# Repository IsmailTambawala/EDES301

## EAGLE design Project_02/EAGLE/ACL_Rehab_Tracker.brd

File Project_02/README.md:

# ACL Rehab Tracker PCB (Project 2)

Compact PCB spin of the Project 1 ACL Rehab Tracker, prepared for fabrication and assembly. This folder holds all design sources and manufacturing outputs.

## Contents
- `ACL Rehab Tracker Schematics.pdf` – quick schematic reference.
- `Docs/` – PDF plots of top/bottom layers and routing.
- `EAGLE/` – editable EAGLE design files (`.sch`, `.brd`, and custom library).
- `ACL_Rehab_Tracker_BOM.csv` – bill of materials for sourcing parts.
- `MFG/CAMOutputs/` – production package:
  - `GerberFiles/` – copper, mask, paste, and silkscreen layers.
  - `DrillFiles/` – NC drill file.
  - `Assembly/` – pick-and-place (front/back) and assembly notes.

## How to build
1) Review the schematic PDF for component intent and placements.  
2) If editing, open `EAGLE/ACL_Rehab_Tracker.sch` and `.brd`, then regenerate CAM if changes are made.  
3) Zip `MFG/CAMOutputs/GerberFiles` and `DrillFiles` for PCB fab.  
4) Send `MFG/CAMOutputs/Assembly` files with the BOM to your assembler for PnP.  
5) Use the Project 1 firmware/software with this board; no firmware changes are required for a fab-only spin.

## Notes
- Designed as a compact, production-ready version of the original prototype.  
- Check part availability against `ACL_Rehab_Tracker_BOM.csv` before ordering to avoid substitutions.  
- If your fab expects a single archive, include the gerbers, drill, and both PnP files.

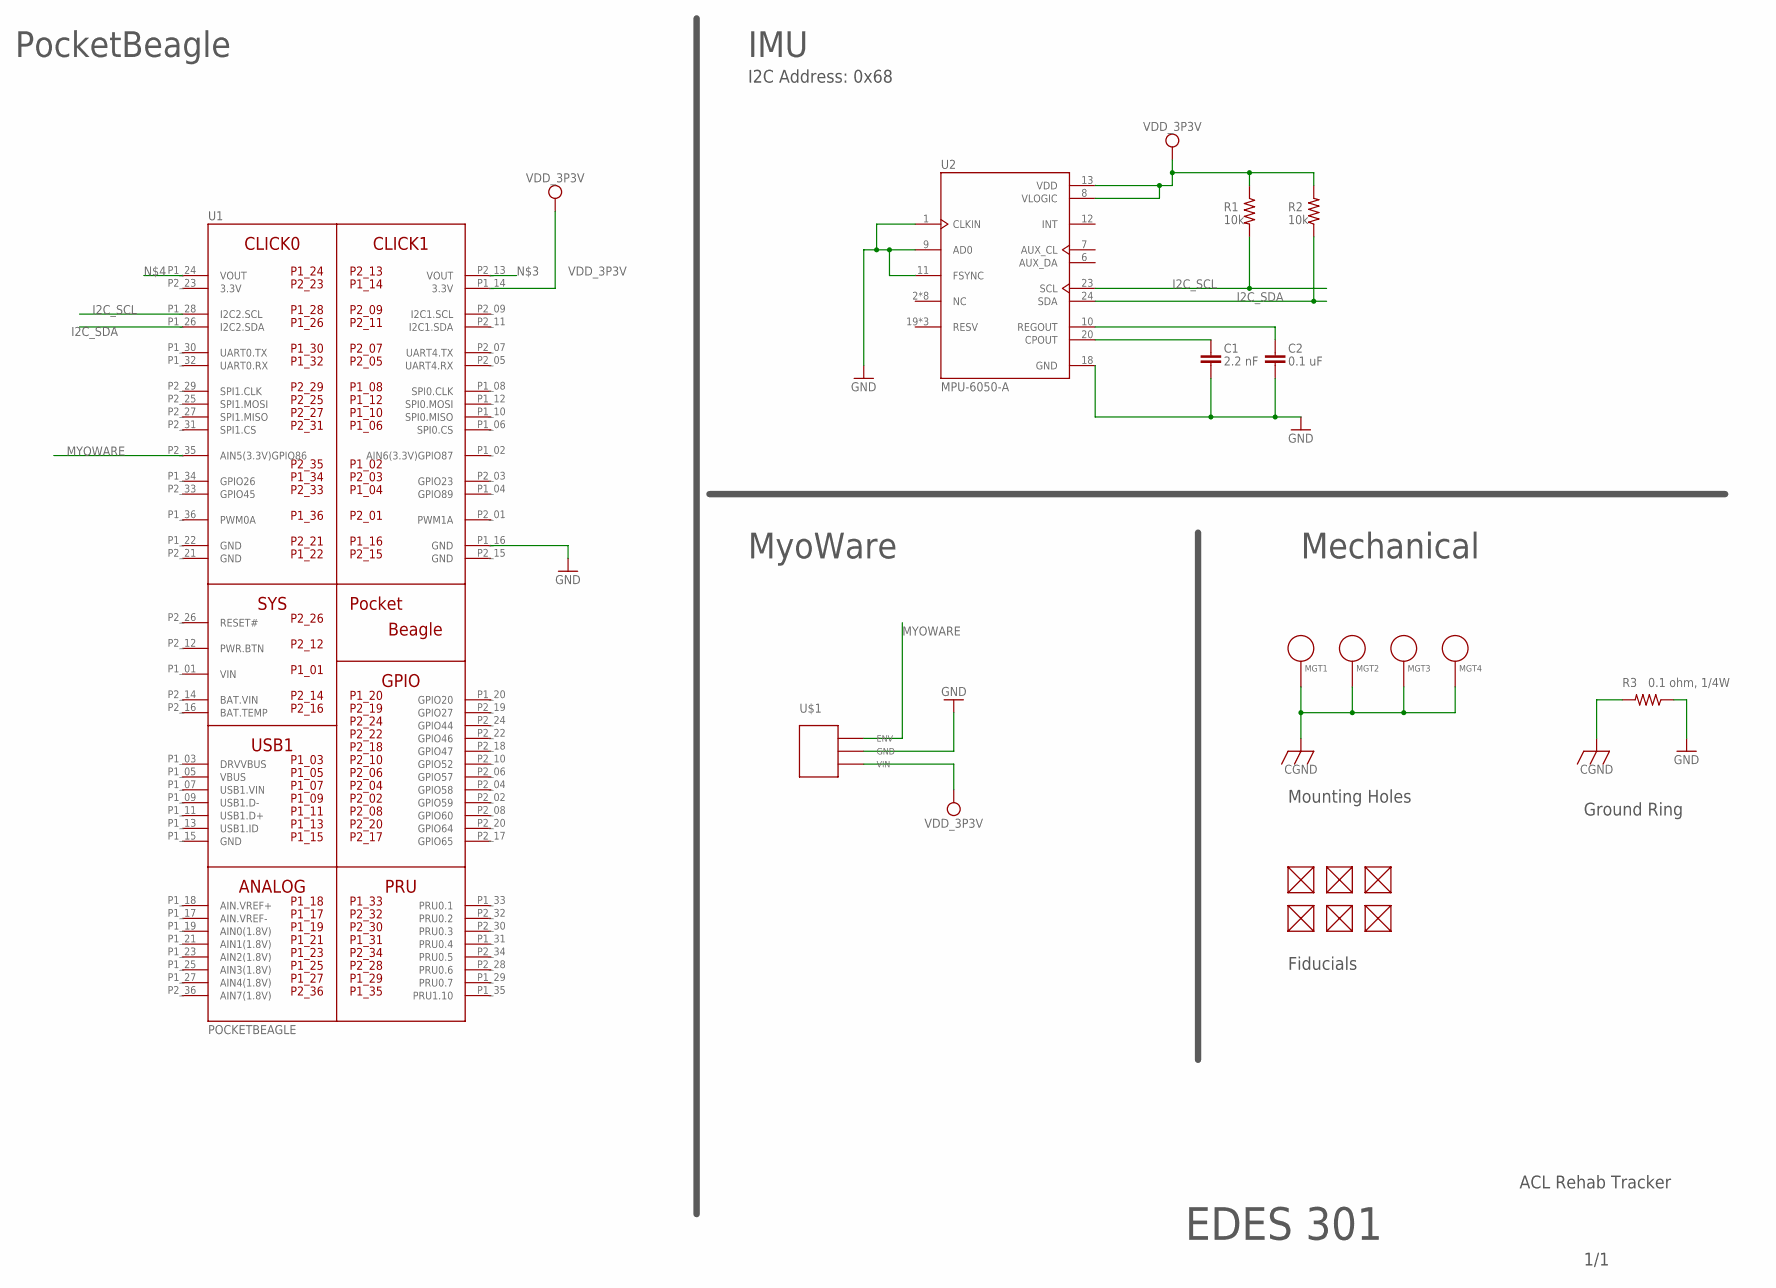
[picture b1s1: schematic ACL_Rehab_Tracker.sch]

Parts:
C1: 2.2 nF; C0603
C2: 0.1 uF; C0603
FUD1, FUD2, FUD3, FUD4, FUD5, FUD6: FIDUCIAL; FIDUCIAL_40MIL
MGT1, MGT2, MGT3, MGT4: MOUNTING_HOLE
R1, R2: 10k; R0603
R3: 0.1 ohm, 1/4W; R0603
U1: POCKETBEAGLE
U2: MPU-6050-A; QFN50P400X400X95-24N
U$1: MYOWARE-2.0-MUSCLE; MYOWARE-3PIN-THR

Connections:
3.3V: U1.P2_23 (3.3V)
BAT.VIN: U1.P2_14 (BAT.VIN)
CGND: MGT1.P$1, MGT2.P$1, MGT3.P$1, MGT4.P$1, R3.2
GND: C1.2, C2.2, R3.1, U1.P1_16 (GND), U1.P1_22 (GND), U1.P2_15 (GND), U1.P2_21 (GND), U2.1 (CLKIN), U2.9 (AD0), U2.11 (FSYNC), U2.18 (GND), U$1.2
I2C_SCL: R1.2, U1.P1_28 (I2C2.SCL), U2.23 (SCL)
I2C_SDA: R2.1, U1.P1_26 (I2C2.SDA), U2.24 (SDA)
MYOWARE: U1.P2_35 (AIN5(3.3V)GPIO86), U$1.1
unnamed: C1.1, U2.20 (CPOUT)
unnamed: C2.1, U2.10 (REGOUT)
VDD_3P3V: R1.1, R2.2, U1.P1_14 (3.3V), U2.8 (VLOGIC), U2.13 (VDD), U$1.3
VIN: U1.P1_01 (VIN)

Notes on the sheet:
PocketBeagle
IMU
MyoWare
I2C Address: 0x68
ACL Rehab Tracker
1/1
EDES 301
Mechanical
Ground Ring
Mounting Holes
Fiducials

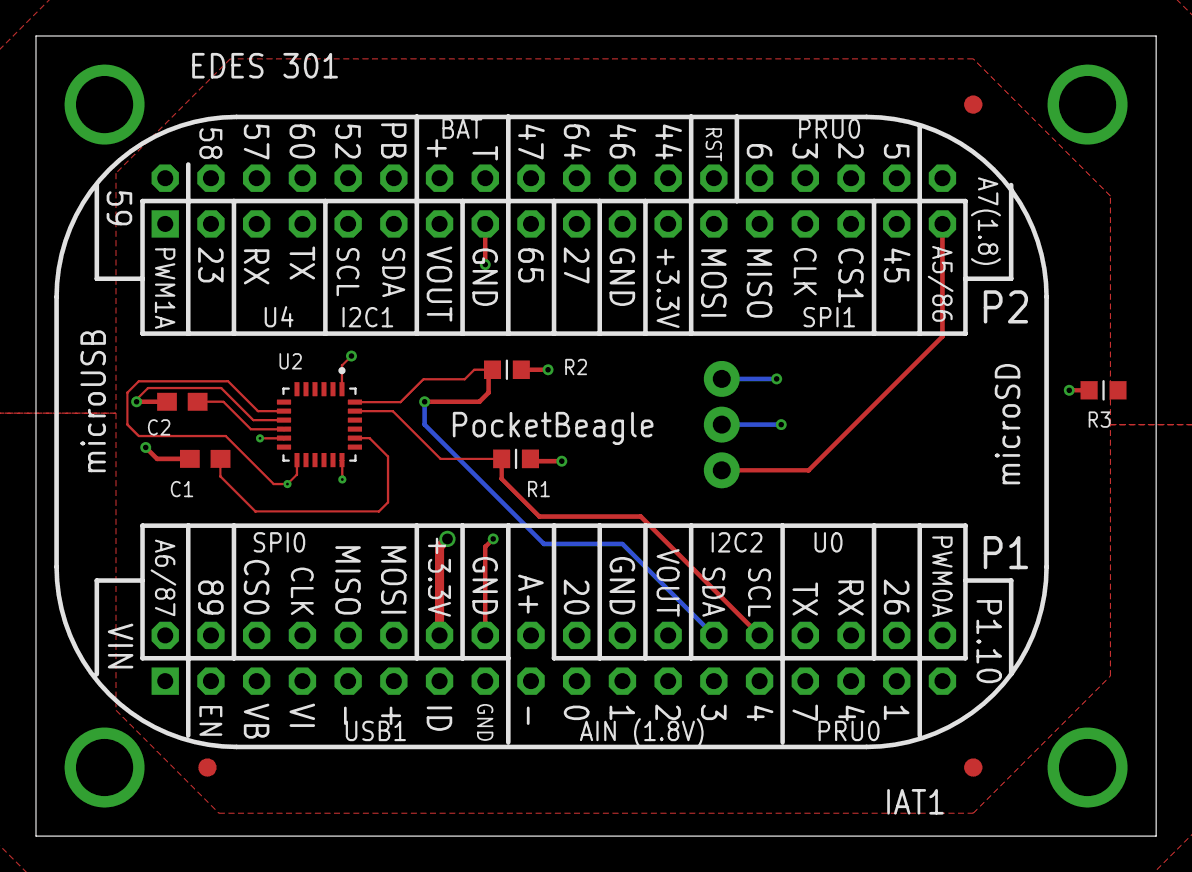
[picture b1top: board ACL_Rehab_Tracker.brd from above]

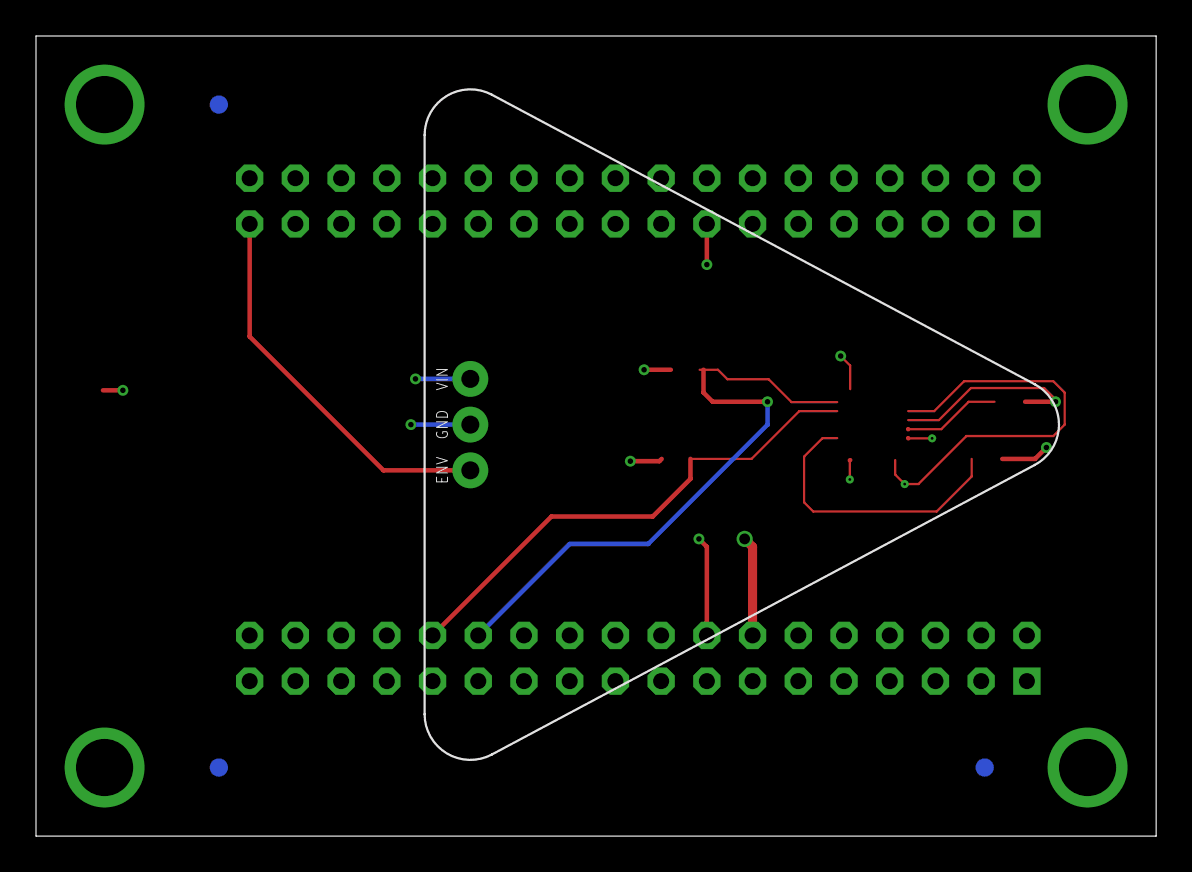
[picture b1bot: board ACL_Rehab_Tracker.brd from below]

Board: 4 copper layers, 62.2 x 44.5 mm, 18 parts (4 on the bottom side), 8 nets.

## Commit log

2025-10-07 Add python folder with new simple calc
2025-10-08 new files button and blink_led
2025-10-08 update to button file
2025-12-03 Adding in codebase for ACL_Rehab_Tracker Project
2025-12-03 did not push correctly
2025-12-03 trying to save work after git history got messed up
2025-12-03 deleting unnecessary files
2025-12-03 Final code of ACL rehab device
2025-12-03 Adding in Demo Video
2025-12-03 updates to readme
2025-12-03 removing video in wrong folder
2025-12-03 Adding demo video to project folder
2025-12-17 initializing folders and saving progress before update
2025-12-17 Final Project_02
2025-12-17 added readme
